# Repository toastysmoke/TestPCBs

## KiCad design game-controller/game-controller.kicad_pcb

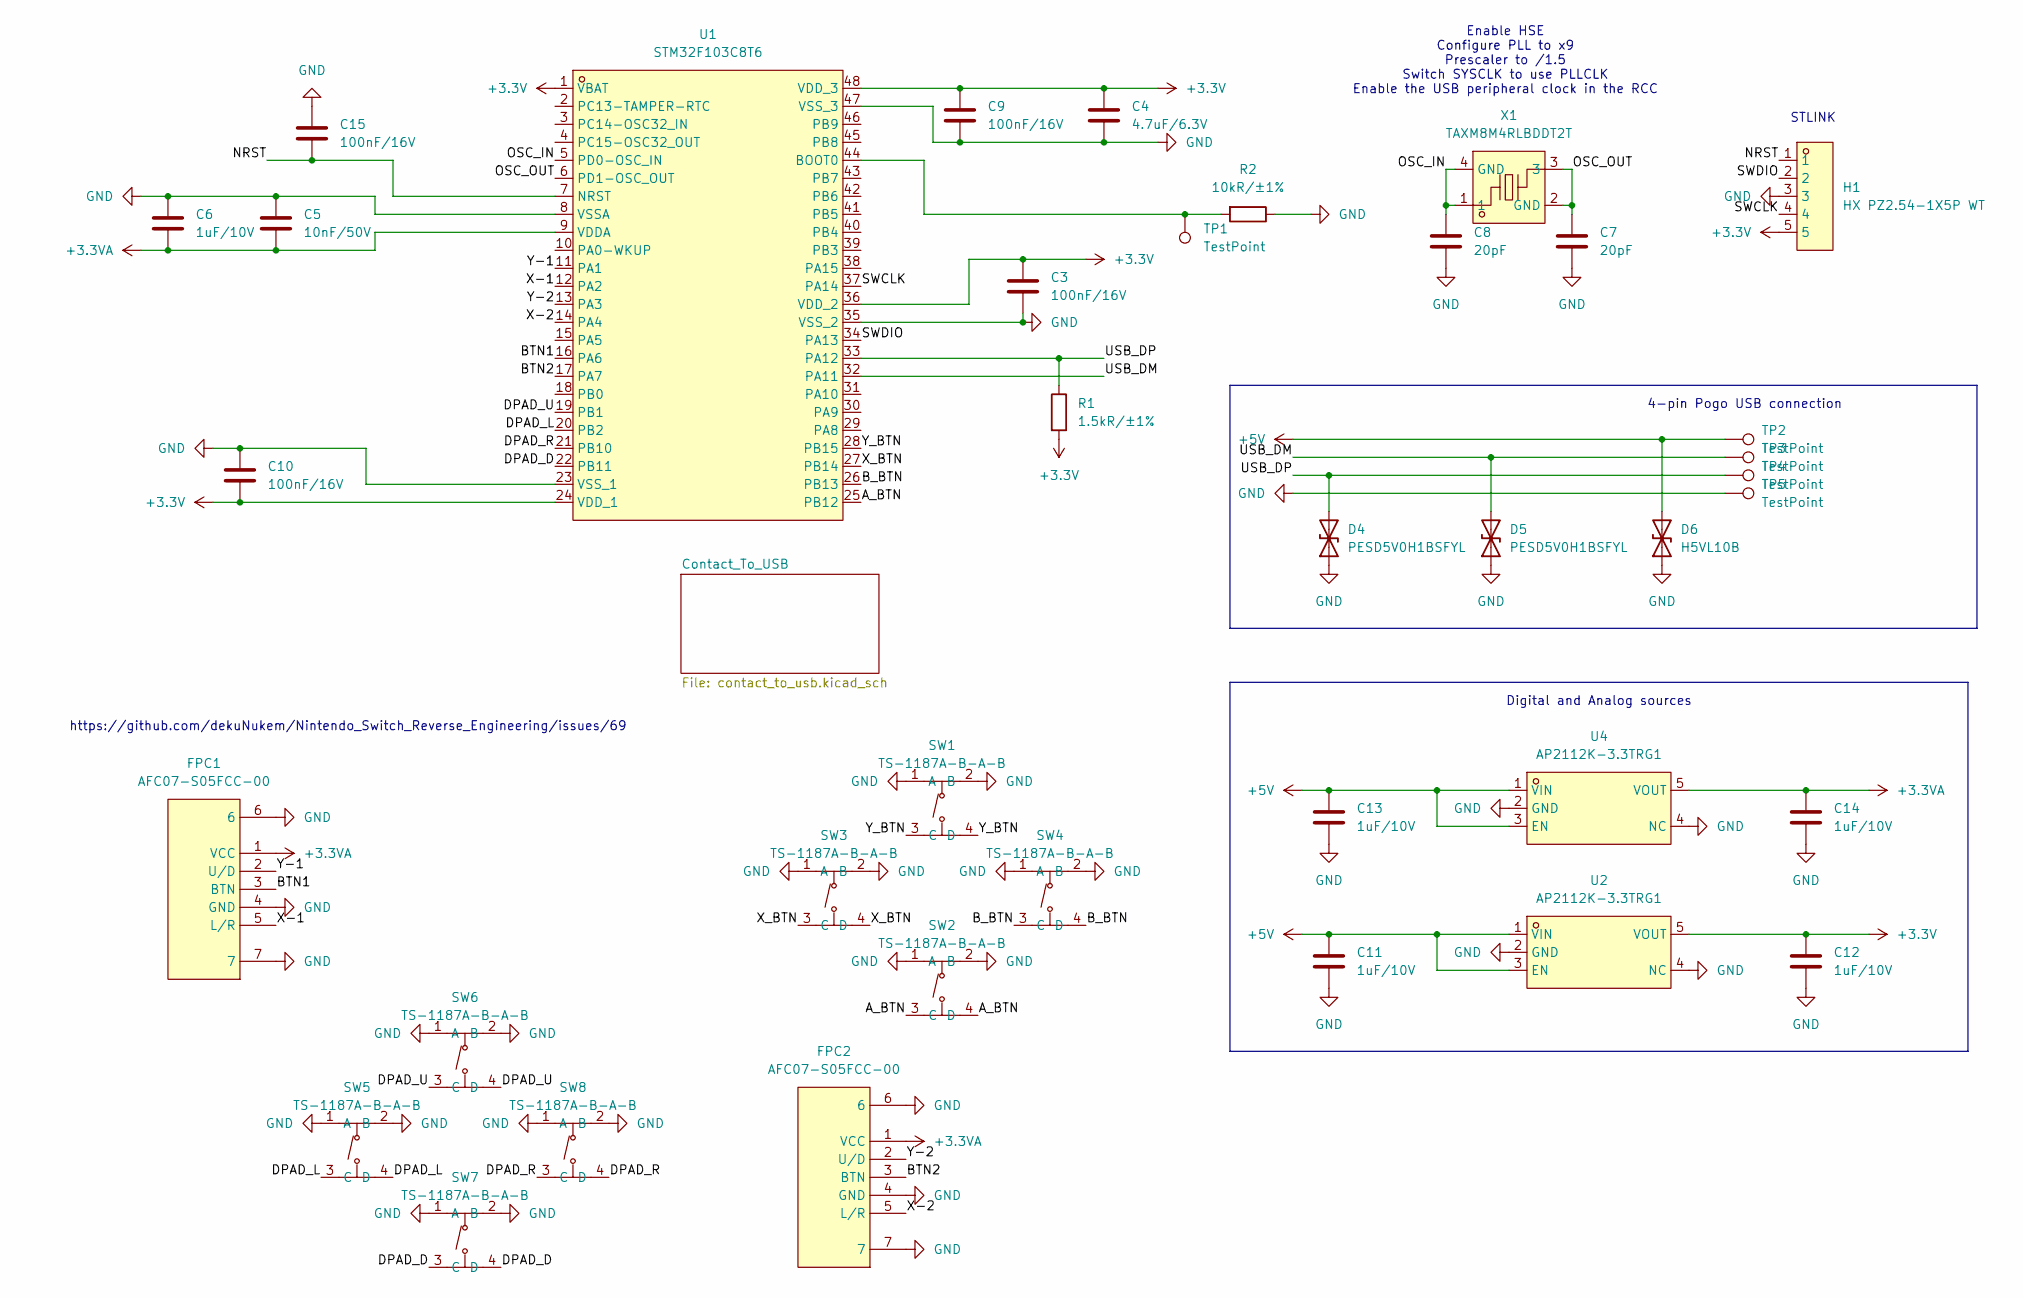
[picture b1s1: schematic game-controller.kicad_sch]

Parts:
C3, C9, C10, C15: 100nF/16V; C_0402_1005Metric; LCSC Part C328914
C4: 4.7uF/6.3V; C_0402_1005Metric; LCSC Part C380302
C5: 10nF/50V; C_0402_1005Metric; LCSC Part C5137480
C6, C11, C12, C13, C14: 1uF/10V; C_0402_1005Metric; LCSC Part C22399609
C7, C8: 20pF; C_0402_1005Metric; LCSC Part C107000
D4, D5: PESD5V0H1BSFYL; Nexperia_DSN0603-2_0.6x0.3mm_P0.4mm; LCSC Part C478002
D6: H5VL10B; D_SOD-882; LCSC Part C7420372
FPC1, FPC2: AFC07-S05FCC-00; FPC-SMD_AFC07-S05FCC-00; MPN AFC07-S05FCC-00; LCSC Part C262199
H1: HX PZ2.54-1X5P WT; HDR-SMD_5P-P2.54-H-M-W12.8-N; MPN HX PZ2.54-1x5P WT; LCSC Part C46061678
R1: 1.5kR/±1%; R_0603_1608Metric; LCSC Part C2930050
R2: 10kR/±1%; R_0402_1005Metric; LCSC Part C2906861
SW1, SW2, SW3, SW4, SW5, SW6, SW7, SW8: TS-1187A-B-A-B; SW-SMD_4P-L5.1-W5.1-P3.70-LS6.5-TL_H1.5; MPN TS-1187A-B-A-B; LCSC Part C318884
TP1: TestPoint; TestPoint_Pad_1.5x1.5mm
TP2, TP3, TP4, TP5: TestPoint; TestPoint_Pad_D3.0mm
U1: STM32F103C8T6; LQFP-48_L7.0-W7.0-P0.50-LS9.0-BL; MPN STM32F103C8T6; LCSC Part C8734
U2, U4: AP2112K-3.3TRG1; SOT-25-5_L2.9-W1.6-P0.95-LS2.8-BL; MPN AP2112K-3.3TRG1; LCSC Part C51118
X1: TAXM8M4RLBDDT2T; CRYSTAL-SMD_4P-L3.2-W2.5-BL; MPN TAXM8M4RLBDDT2T; LCSC Part C720915

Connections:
+3.3V: C3.1, C4.1, C9.1, C10.2, C12.1, H1.5, R1.2, U1.1 (VBAT), U1.24 (VDD_1), U1.36 (VDD_2), U1.48 (VDD_3), U2.5 (VOUT)
+3.3VA: C5.2, C6.2, C14.1, FPC1.1 (VCC), FPC2.1 (VCC), U1.9 (VDDA), U4.5 (VOUT)
+5V: C11.1, C13.1, D6.2 (A2), TP2.1 (1_1), U2.1 (VIN), U2.3 (EN), U4.1 (VIN), U4.3 (EN)
/A_BTN: SW2.3 (C), SW2.4 (D), U1.25 (PB12)
/BTN1: FPC1.3 (BTN), U1.16 (PA6)
/BTN2: FPC2.3 (BTN), U1.17 (PA7)
/B_BTN: SW4.3 (C), SW4.4 (D), U1.26 (PB13)
/DPAD_D: SW7.3 (C), SW7.4 (D), U1.22 (PB11)
/DPAD_L: SW5.3 (C), SW5.4 (D), U1.20 (PB2)
/DPAD_R: SW8.3 (C), SW8.4 (D), U1.21 (PB10)
/DPAD_U: SW6.3 (C), SW6.4 (D), U1.19 (PB1)
/NRST: C15.2, H1.1, U1.7 (NRST)
/OSC_IN: C8.1, U1.5 (PD0-OSC_IN), X1.1, X1.4 (GND)
/OSC_OUT: C7.1, U1.6 (PD1-OSC_OUT), X1.2 (GND), X1.3
/SWCLK: H1.4, U1.37 (PA14)
/SWDIO: H1.2, U1.34 (PA13)
/USB_DM: D5.2 (A2), TP3.1 (1_1), U1.32 (PA11)
/USB_DP: D4.2 (A2), R1.1, TP4.1 (1_1), U1.33 (PA12)
/X-1: FPC1.5 (L/R), U1.12 (PA2)
/X-2: FPC2.5 (L/R), U1.14 (PA4)
/X_BTN: SW3.3 (C), SW3.4 (D), U1.27 (PB14)
/Y-1: FPC1.2 (U/D), U1.11 (PA1)
/Y-2: FPC2.2 (U/D), U1.13 (PA3)
/Y_BTN: SW1.3 (C), SW1.4 (D), U1.28 (PB15)
GND: C3.2, C4.2, C5.1, C6.1, C7.2, C8.2, C9.2, C10.1, C11.2, C12.2, C13.2, C14.2, C15.1, D4.1 (A1), D5.1 (A1), D6.1 (A1), FPC1.4 (GND), FPC1.6, FPC1.7, FPC2.4 (GND), FPC2.6, FPC2.7, H1.3, R2.1, SW1.1 (A), SW1.2 (B), SW2.1 (A), SW2.2 (B), SW3.1 (A), SW3.2 (B), SW4.1 (A), SW4.2 (B), SW5.1 (A), SW5.2 (B), SW6.1 (A), SW6.2 (B), SW7.1 (A), SW7.2 (B), SW8.1 (A), SW8.2 (B), TP5.1 (1_1), U1.8 (VSSA), U1.23 (VSS_1), U1.35 (VSS_2), U1.47 (VSS_3), U2.2 (GND), U2.4 (NC), U4.2 (GND), U4.4 (NC); also elsewhere on the board
unnamed: R2.2, TP1.1 (1_1), U1.44 (BOOT0)

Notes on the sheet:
https://github.com/dekuNukem/Nintendo_Switch_Reverse_Engineering/issues/69
4-pin Pogo USB connection
Digital and Analog sources
STLINK
Enable HSE Configure PLL to x9 Prescaler to /1.5 Switch SYSCLK to use PLLCLK Enable the USB peripheral clock in the RCC

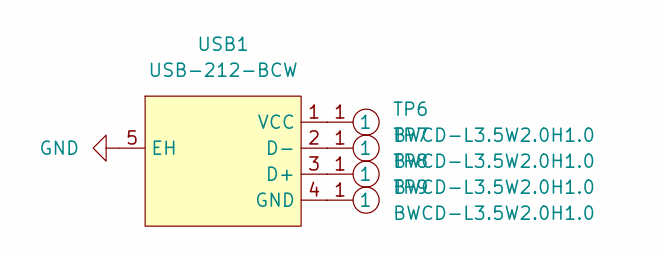
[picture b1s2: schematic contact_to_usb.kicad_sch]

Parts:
TP6, TP7, TP8, TP9: BWCD-L3.5W2.0H1.0; SMD_BD2.0-L2.0-W2.0_C9900001905; MPN BWCD-L3.5W2.0H1.0; LCSC Part C2826547
USB1: USB-212-BCW; USB-A-SMD_USB-212-BCW; MPN USB-212-BCW; LCSC Part C720521

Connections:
GND: USB1.5 (EH); also elsewhere on the board
unnamed: TP8.1 (1_1), USB1.3 (D+)
unnamed: TP7.1 (1_1), USB1.2 (D-)
unnamed: TP9.1 (1_1), USB1.4 (GND)
unnamed: TP6.1 (1_1), USB1.1 (VCC)

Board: 2 copper layers, 43 parts (29 on the bottom side), 30 nets, no tracks yet.

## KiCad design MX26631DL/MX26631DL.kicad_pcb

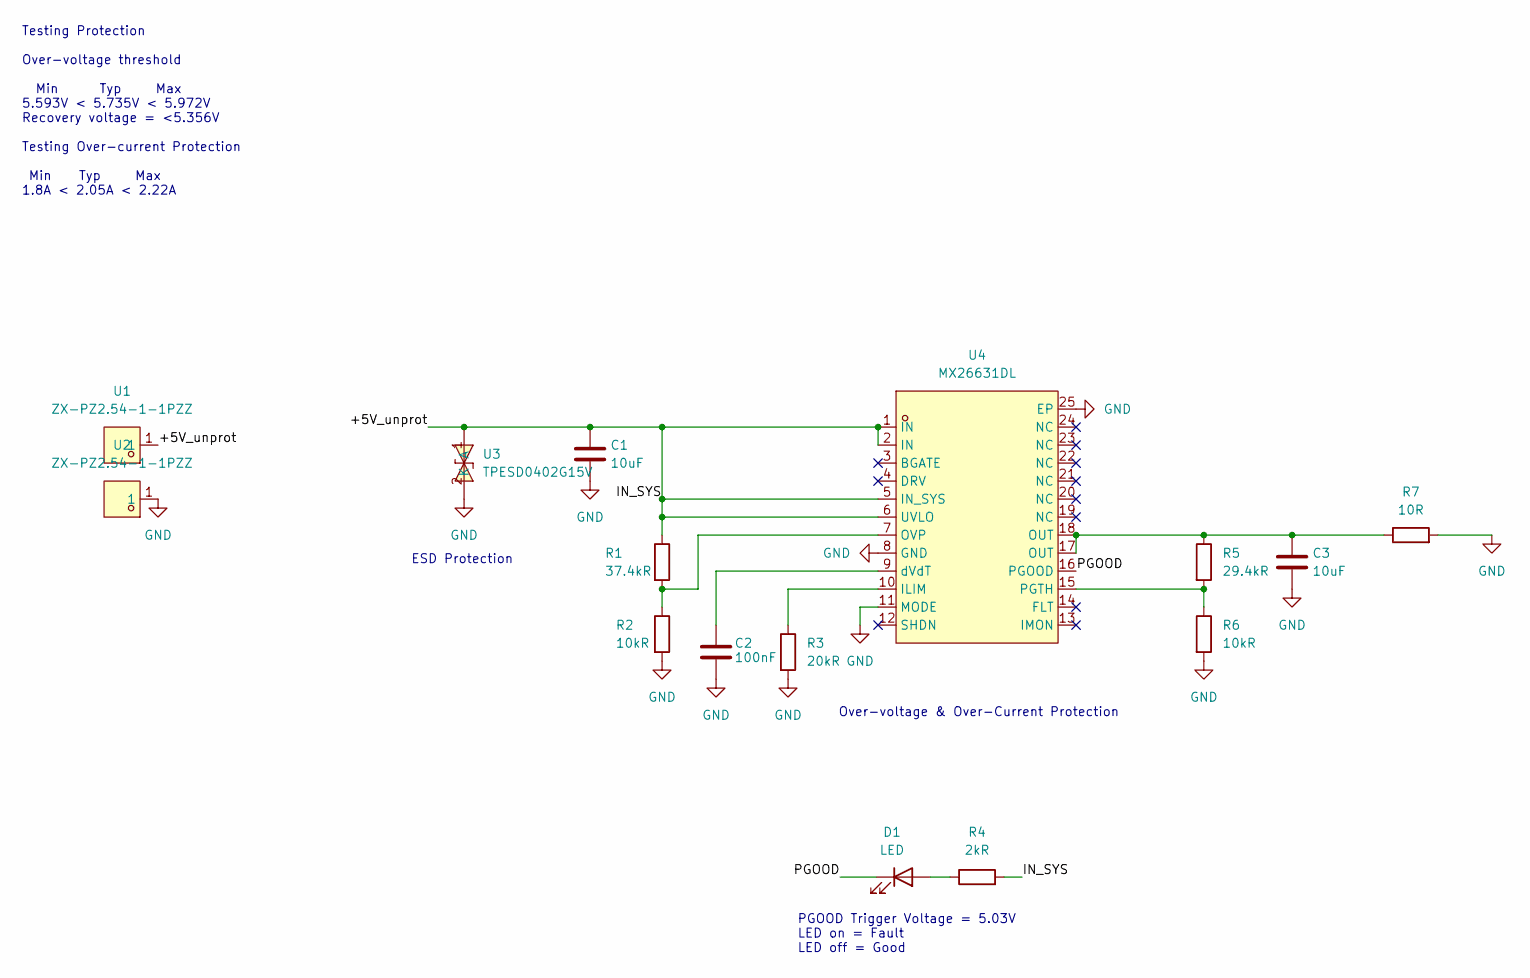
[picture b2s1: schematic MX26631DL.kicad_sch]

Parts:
C1, C3: 10uF; C_0805_2012Metric_Pad1.18x1.45mm_HandSolder; LCSC Part C95841
C2: 100nF; C_0402_1005Metric_Pad0.74x0.62mm_HandSolder; LCSC Part C307331
D1: LED; LED_0603_1608Metric; LCSC Part C965799
R1: 37.4kR; R_0402_1005Metric_Pad0.72x0.64mm_HandSolder; LCSC Part C185422
R2, R6: 10kR; R_0402_1005Metric_Pad0.72x0.64mm_HandSolder; LCSC Part C60490
R3: 20kR; R_0603_1608Metric_Pad0.98x0.95mm_HandSolder; LCSC Part C2907011
R4: 2kR; R_0603_1608Metric; LCSC Part C22975
R5: 29.4kR; R_0603_1608Metric; LCSC Part C2930086
R7: 10R; R_2512_6332Metric_Pad1.40x3.35mm_HandSolder; LCSC Part C2075790
U1, U2: ZX-PZ2.54-1-1PZZ; HDR-TH_1P-P2.54-V-M; MPN ZX-PZ2.54-1-1PZZ; LCSC Part C7501259
U3: TPESD0402G15V; D_0402_1005Metric; LCSC Part C558618
U4: MX26631DL; QFN-24_L4.0-W4.0-P0.50-TL-EP2.7; LCSC Part C18197523

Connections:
/+5V_unprot: C1.1, R1.1, R4.2, U1.1, U3.1 (K), U4.1 (IN), U4.2 (IN), U4.5 (IN_SYS), U4.6 (UVLO)
/PGOOD: D1.1 (K), U4.16 (PGOOD)
GND: C1.2, C2.1, C3.2, R2.2, R3.2, R6.2, R7.2, U2.1, U3.2 (A), U4.8 (GND), U4.11 (MODE), U4.25 (EP)
unnamed: C3.1, R5.1, R7.1, U4.17 (OUT), U4.18 (OUT)
unnamed: D1.2 (A), R4.1
unnamed: R3.1, U4.10 (ILIM)
unnamed: R1.2, R2.1, U4.7 (OVP)
unnamed: R5.2, R6.1, U4.15 (PGTH)
unnamed: C2.2, U4.9 (dVdT)

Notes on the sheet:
PGOOD Trigger Voltage = 5.03V LED on = Fault LED off = Good
Over-voltage & Over-Current Protection
Testing Protection Over-voltage threshold Min Typ Max 5.593V < 5.735V < 5.972V Recovery voltage = <5.356V Testing Over-current Protection Min Typ Max 1.8A < 2.05A < 2.22A
ESD Protection

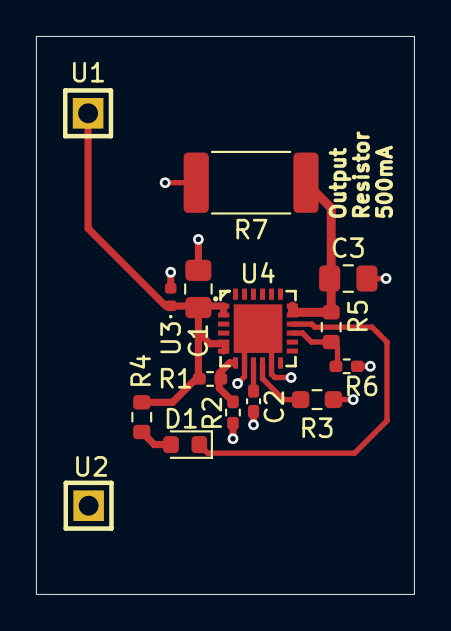
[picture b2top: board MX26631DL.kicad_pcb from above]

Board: 2 copper layers, 21.0 x 31.0 mm, 15 parts (0 on the bottom side), 9 nets.

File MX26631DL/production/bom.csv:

Designator,Footprint,Quantity,Value,LCSC Part #
"C1, C3",0805,2,10uF,C95841
C2,0402,1,100nF,C307331
D1,0603,1,LED,C965799
R1,0402,1,37.4kR,C185422
"R2, R6",0402,2,10kR,C60490
R3,0603,1,20kR,C2907011
R4,0603,1,2kR,C22975
R5,0603,1,29.4kR,C2930086
R7,2512,1,10R,C2075790
"U1, U2",HDR-TH_1P-P2.54-V-M,2,ZX-PZ2.54-1-1PZZ,C7501259
U3,0402,1,TPESD0402G15V,C558618
U4,QFN-24_L4.0-W4.0-P0.50-TL-EP2.7,1,MX26631DL,C18197523

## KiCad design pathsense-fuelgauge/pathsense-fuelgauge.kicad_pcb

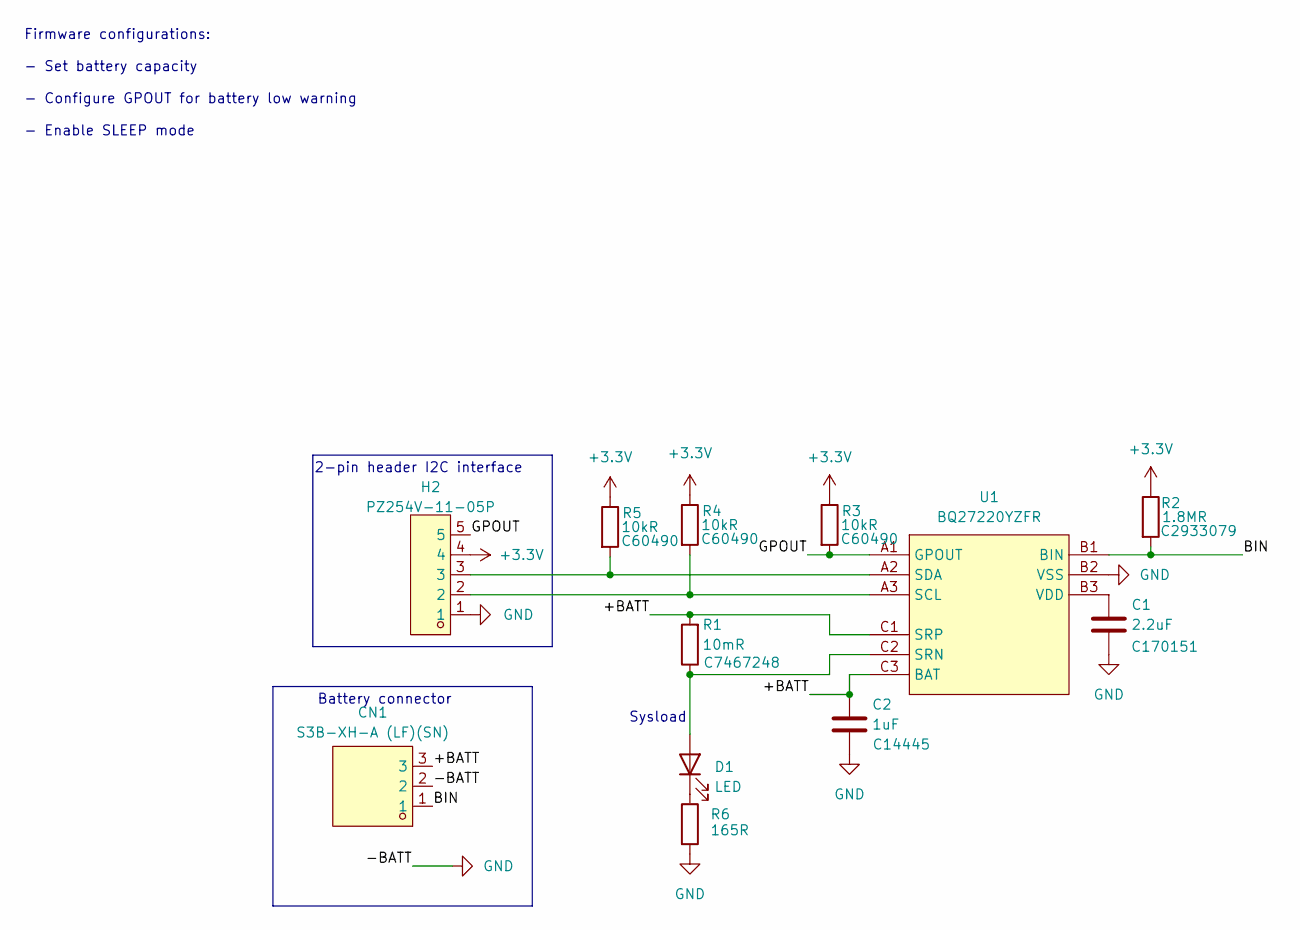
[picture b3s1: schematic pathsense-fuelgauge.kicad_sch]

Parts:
C1: 2.2uF; C_0402_1005Metric_Pad0.74x0.62mm_HandSolder; LCSC Part C170151
C2: 1uF; C_0402_1005Metric_Pad0.74x0.62mm_HandSolder; LCSC Part C14445
CN1: S3B-XH-A (LF)(SN); JST-S3B-XH-A(LF)(SN); LCSC Part C157928
D1: LED; LED_0603_1608Metric; LCSC Part C965807
H2: PZ254V-11-05P; XFCN-PZ254V-11-05P; LCSC Part C492404
R1: 10mR; R_1206_3216Metric_Pad1.30x1.75mm_HandSolder; LCSC Part C7467248
R2: 1.8MR; R_0402_1005Metric_Pad0.72x0.64mm_HandSolder; LCSC Part C2933079
R3, R4, R5: 10kR; R_0402_1005Metric_Pad0.72x0.64mm_HandSolder; LCSC Part C60490
R6: 165R; R_0603_1608Metric_Pad0.98x0.95mm_HandSolder; LCSC Part C861151
U1: BQ27220YZFR; TI-BQ27220YZFR; LCSC Part C528617

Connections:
+3.3V: H2.4, R2.1, R3.1, R4.1, R5.1
/+BATT: C2.1, CN1.3, R1.2, U1.C1 (SRP), U1.C3 (BAT)
/BIN: CN1.1, R2.2, U1.B1 (BIN)
/GPOUT: H2.5, R3.2, U1.A1 (GPOUT)
GND: C1.1, C2.2, CN1.2, H2.1, R6.2, U1.B2 (VSS)
unnamed: D1.2 (A), R1.1, U1.C2 (SRN)
unnamed: D1.1 (K), R6.1
unnamed: H2.2, R4.2, U1.A3 (SCL)
unnamed: H2.3, R5.2, U1.A2 (SDA)
unnamed: C1.2, U1.B3 (VDD)

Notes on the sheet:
Firmware configurations: - Set battery capacity - Configure GPOUT for battery low warning - Enable SLEEP mode
2-pin header I2C interface
Battery connector
Sysload

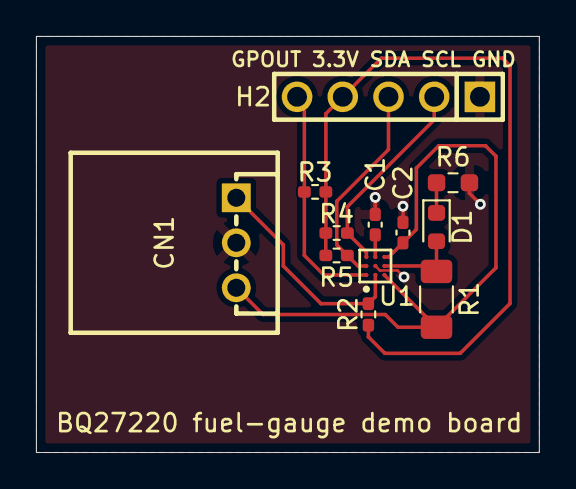
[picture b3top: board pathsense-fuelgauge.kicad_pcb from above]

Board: 2 copper layers, 27.9 x 23.1 mm, 12 parts (0 on the bottom side), 10 nets.

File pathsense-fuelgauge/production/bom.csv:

Designator,Footprint,Quantity,Value,LCSC Part #
C1,0402,1,2.2uF,C170151
C2,0402,1,1uF,C14445
CN1,JST-S3B-XH-A(LF)(SN),1,S3B-XH-A (LF)(SN),C157928
D1,0603,1,LED,C965807
H2,XFCN-PZ254V-11-05P,1,PZ254V-11-05P,C492404
R1,1206,1,10mR,C7467248
R2,0402,1,1.8MR,C2933079
"R3, R4, R5",0402,3,10kR,C60490
R6,0603,1,165R,C861151
U1,TI-BQ27220YZFR,1,BQ27220YZFR,C528617

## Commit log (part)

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2025-11-29 Work in progress...
2025-11-29 Cleaned stable branch
2026-01-11 Working on schematic
2026-01-13 Completed more connections WIP
2026-02-13 Start of IC protection circuit
2026-02-14 Finished PCB with production files
2026-02-14 Changed capacitor size
2026-02-14 Made slight changes with latest production files
2026-02-21 Testboard is done, production files generated
2026-03-03 Removed Ground pour for easier sodering
2026-03-06 Revert "Removed Ground pour for easier sodering"
    This reverts commit 94e415ae81cb2b8cab0b706f2261028b2c6a871a.
2026-03-16 Added dVdT capacitor to reduce current inrush. Production files generated
2026-05-18 Adding gitignore
2026-05-18 Removed backups from remote
2026-05-18 Fixed gitignore
2026-05-18 Properly removed backups from git
2026-05-27 Need to verify circuit 1 more time
2026-05-28 Time to test
2026-05-29 Changed dimensions slightly
2026-05-29 New iteration done
